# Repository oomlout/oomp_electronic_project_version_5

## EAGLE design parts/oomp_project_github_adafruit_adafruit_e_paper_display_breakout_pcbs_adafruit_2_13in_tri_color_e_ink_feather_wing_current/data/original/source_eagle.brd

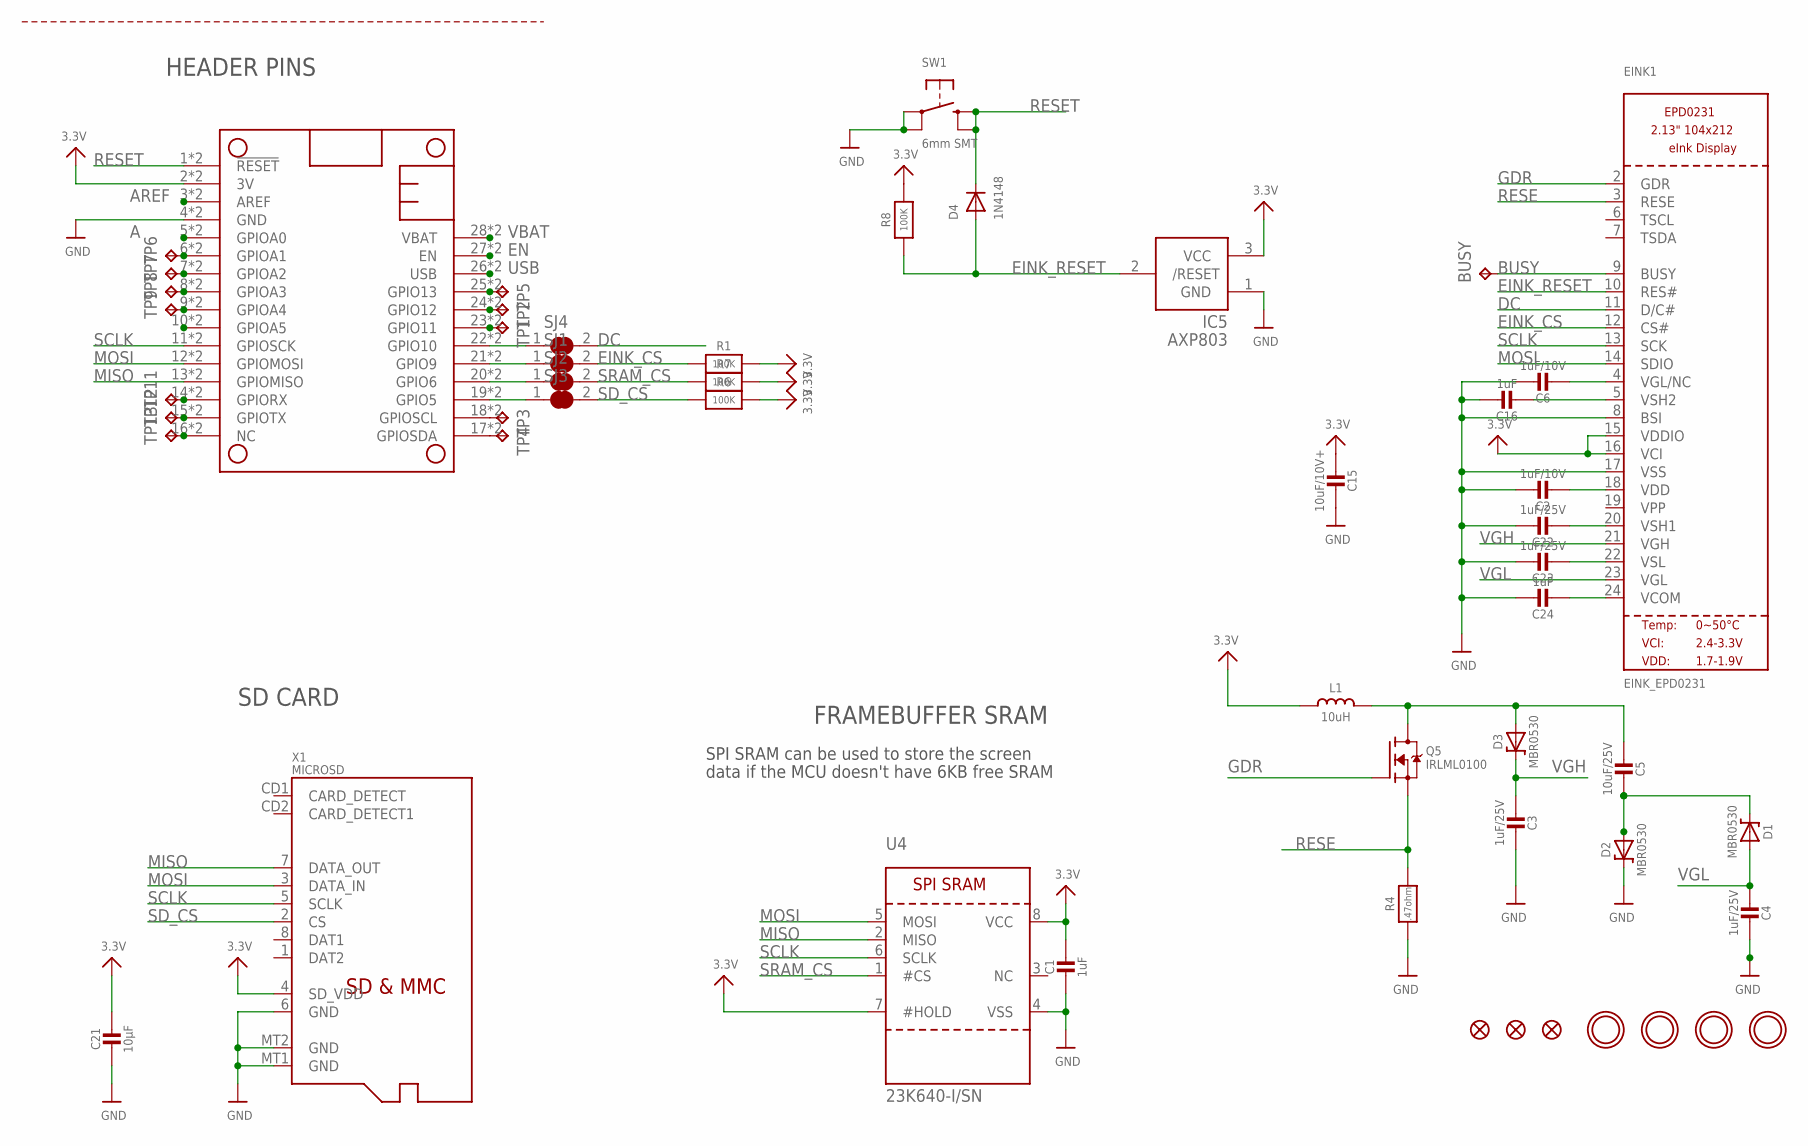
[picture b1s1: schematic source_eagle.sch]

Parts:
BUSY: TPTP15SQ; TP15SQ
C1: 1uF; 0805_10MGAP
C2, C6: 1uF/10V; 0805-NO
C3, C4, C22, C23: 1uF/25V; 0805-NO
C5: 10uF/25V; 0805-NO
C15: 10uF/10V+; 0805-NO
C16, C24: 1uF; 0805-NO
C21: 10µF; 0805-NO
D1, D2, D3: MBR0530; SOD-123
D4: 1N4148; SOD-323F
EINK1: EINK_EPD0231; EINK_213IN_104X212
FID1, FID2, FID3: FIDUCIAL_1MM
IC5: AXP803; SOT23
L1: 10uH; INDUCTOR_4X4MM_NR401
MS1: FEATHERWING_SMTDUALNOHOLES; FEATHERWING_SMT_NOHOLES
Q5: IRLML0100; SOT23-3
R1, R6, R7, R8: 100K; 0603-NO
R4: .47ohm; 0805_10MGAP
SJ1, SJ2, SJ3, SJ4: SOLDERJUMPER_CLOSED; SOLDERJUMPER_CLOSEDWIRE
SW1: 6mm SMT; EVQ-Q2_SMALLER
TP1, TP2, TP3, TP4, TP5, TP6, TP7, TP8, TP9, TP11, TP12, TP13: TPTP15SQ; TP15SQ
U4: 23K640-I/SN; SOIC8_150MIL
U$3, U$4, U$5, U$6: MOUNTINGHOLE2.5; MOUNTINGHOLE_2.5_PLATED
X1: MICROSD

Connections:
3.3V: C1.1, C15.2, C21.1, EINK1.15 (VDDIO), EINK1.16 (VCI), IC5.3 (VCC), L1.P$2 (2), MS1.2 (3V), MS1.2B (3V), R1.2, R6.2, R7.2, R8.2, U4.7 (#HOLD), U4.8 (VCC), X1.4 (SD_VDD)
A: MS1.5 (GPIOA0), MS1.5B (GPIOA0)
AREF: MS1.3 (AREF), MS1.3B (AREF)
B: MS1.6 (GPIOA1), MS1.6B (GPIOA1), TP6.TP
BUSY: BUSY.TP, EINK1.9 (BUSY)
C: MS1.7 (GPIOA2), MS1.7B (GPIOA2), TP7.TP
D: MS1.8 (GPIOA3), MS1.8B (GPIOA3), TP8.TP
DC: EINK1.11 (D/C#), SJ4.2
E: MS1.9 (GPIOA4), MS1.9B (GPIOA4), TP9.TP
EINK_CS: EINK1.12 (CS#), R1.1, SJ1.2
EINK_RESET: D4.A, EINK1.10 (RES#), IC5.2 (/RESET), R8.1
EN: MS1.27 (EN), MS1.27B (EN)
F: MS1.10 (GPIOA5), MS1.10B (GPIOA5)
G: MS1.16 (NC), MS1.16B (NC), TP13.TP
GDR: EINK1.2 (GDR), Q5.1 (G)
GND: C1.2, C2.1, C3.2, C4.2, C6.1, C15.1, C16.1, C21.2, C22.1, C23.1, C24.1, D2.C, EINK1.8 (BSI), EINK1.17 (VSS), IC5.1 (GND), MS1.4 (GND), MS1.4B (GND), R4.2, SW1.A, SW1.A' (P1), U4.4 (VSS), X1.6 (GND), X1.MT1 (GND), X1.MT2 (GND)
H: MS1.19 (GPIO5), MS1.19B (GPIO5), SJ3.1
I: MS1.20 (GPIO6), MS1.20B (GPIO6), SJ2.1
J: MS1.21 (GPIO9), MS1.21B (GPIO9), SJ1.1
K: MS1.22 (GPIO10), MS1.22B (GPIO10), SJ4.1
L: MS1.23 (GPIO11), MS1.23B (GPIO11), TP1.TP
M: MS1.24 (GPIO12), MS1.24B (GPIO12), TP2.TP
MISO: MS1.13 (GPIOMISO), MS1.13B (GPIOMISO), U4.2 (MISO), X1.7 (DATA_OUT)
MOSI: EINK1.14 (SDIO), MS1.12 (GPIOMOSI), MS1.12B (GPIOMOSI), U4.5 (MOSI), X1.3 (DATA_IN)
N: MS1.25 (GPIO13), MS1.25B (GPIO13), TP5.TP
unnamed: C5.2, D1.C, D2.A
unnamed: C5.1, D3.A, L1.P$1 (1), Q5.3 (D)
unnamed: C16.2, EINK1.5 (VSH2)
unnamed: C2.2, EINK1.18 (VDD)
unnamed: C22.2, EINK1.20 (VSH1)
unnamed: C6.2, EINK1.4 (VGL/NC)
unnamed: C23.2, EINK1.22 (VSL)
unnamed: C24.2, EINK1.24 (VCOM)
RESE: EINK1.3 (RESE), Q5.2 (S), R4.1
RESET: D4.C, MS1.1 (!RESET), MS1.1B (!RESET), SW1.B (S), SW1.B' (S1)
RX: MS1.14 (GPIORX), MS1.14B (GPIORX), TP11.TP
SCL: MS1.18 (GPIOSCL), MS1.18B (GPIOSCL), TP3.TP
SCLK: EINK1.13 (SCK), MS1.11 (GPIOSCK), MS1.11B (GPIOSCK), U4.6 (SCLK), X1.5 (SCLK)
SDA: MS1.17 (GPIOSDA), MS1.17B (GPIOSDA), TP4.TP
SD_CS: R6.1, SJ3.2, X1.2 (CS)
SRAM_CS: R7.1, SJ2.2, U4.1 (#CS)
TX: MS1.15 (GPIOTX), MS1.15B (GPIOTX), TP12.TP
USB: MS1.26 (USB), MS1.26B (USB)
VBAT: MS1.28 (VBAT), MS1.28B (VBAT)
VGH: C3.1, D3.C, EINK1.21 (VGH)
VGL: C4.1, D1.A, EINK1.23 (VGL)

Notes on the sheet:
HEADER PINS
FRAMEBUFFER SRAM
SPI SRAM can be used to store the screen
data if the MCU doesn't have 6KB free SRAM
SD CARD

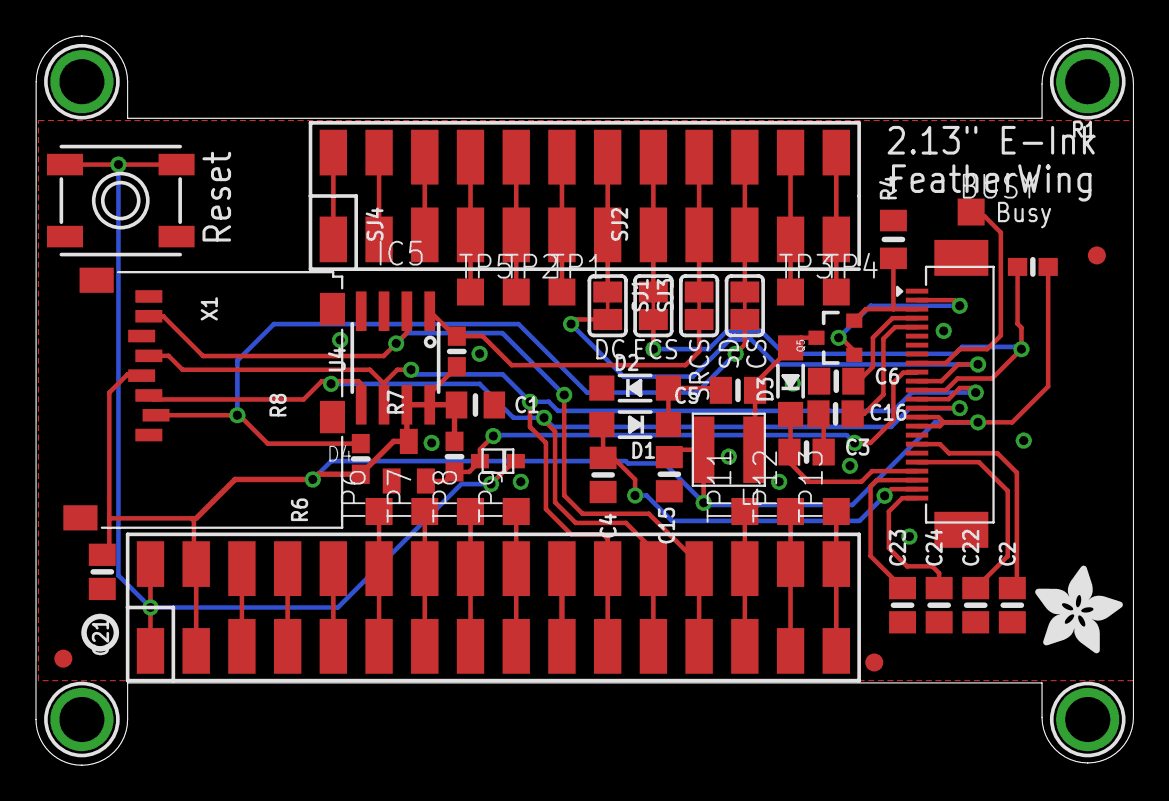
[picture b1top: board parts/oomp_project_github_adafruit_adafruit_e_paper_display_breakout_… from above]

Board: 2 copper layers, 61.0 x 40.5 mm, 55 parts (1 on the bottom side), 46 nets.

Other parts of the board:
U$8: ADAFRUIT_5MM
U$9: PCBFEAT-REV-040

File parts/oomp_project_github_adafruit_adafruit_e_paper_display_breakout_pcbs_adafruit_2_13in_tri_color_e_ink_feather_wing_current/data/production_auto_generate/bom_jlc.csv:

Comment,Designator,Footprint,LCSC Part #
,U$8,Adafruit 2.13in Tri-Color eInk FeatherWing-import-fps:ADAFRUIT_5MM,
,U$9,Adafruit 2.13in Tri-Color eInk FeatherWing-import-fps:PCBFEAT-REV-040,
.47ohm,R4,Adafruit 2.13in Tri-Color eInk FeatherWing-import-fps:0805_10MGAP,
100K,"R1,R6,R7,R8",Adafruit 2.13in Tri-Color eInk FeatherWing-import-fps:0603-NO,C25803
10uF/10V+,C15,Adafruit 2.13in Tri-Color eInk FeatherWing-import-fps:0805-NO,
10uF/25V,C5,Adafruit 2.13in Tri-Color eInk FeatherWing-import-fps:0805-NO,
10uH,L1,Adafruit 2.13in Tri-Color eInk FeatherWing-import-fps:INDUCTOR_4X4MM_NR401,
10µF,C21,Adafruit 2.13in Tri-Color eInk FeatherWing-import-fps:0805-NO,
1N4148,D4,Adafruit 2.13in Tri-Color eInk FeatherWing-import-fps:SOD-323F,
1uF,"C16,C24",Adafruit 2.13in Tri-Color eInk FeatherWing-import-fps:0805-NO,
1uF,C1,Adafruit 2.13in Tri-Color eInk FeatherWing-import-fps:0805_10MGAP,
1uF/10V,"C2,C6",Adafruit 2.13in Tri-Color eInk FeatherWing-import-fps:0805-NO,
1uF/25V,"C3,C4,C22,C23",Adafruit 2.13in Tri-Color eInk FeatherWing-import-fps:0805-NO,
23K640-I/SN,U4,Adafruit 2.13in Tri-Color eInk FeatherWing-import-fps:SOIC8_150MIL,
6mm SMT,SW1,Adafruit 2.13in Tri-Color eInk FeatherWing-import-fps:EVQ-Q2_SMALLER,
AXP803,IC5,Adafruit 2.13in Tri-Color eInk FeatherWing-import-fps:SOT23,
EINK_EPD0231,EINK1,Adafruit 2.13in Tri-Color eInk FeatherWing-import-fps:EINK_213IN_104X212,
FEATHERWING_SMTDUALNOHOLES,MS1,Adafruit 2.13in Tri-Color eInk FeatherWing-import-fps:FEATHERWING_SMT_NOHOLES,
IRLML0100,Q5,Adafruit 2.13in Tri-Color eInk FeatherWing-import-fps:SOT23-3,
MBR0530,"D1,D2,D3",Adafruit 2.13in Tri-Color eInk FeatherWing-import-fps:SOD-123,
MICROSD,X1,Adafruit 2.13in Tri-Color eInk FeatherWing-import-fps:MICROSD,
TPTP15SQ,"BUSY0,TP1,TP2,TP3,TP4,TP5,TP6,TP7,TP8,TP9,TP11,TP12,TP13",Adafruit 2.13in Tri-Color eInk FeatherWing-import-fps:TP15SQ,

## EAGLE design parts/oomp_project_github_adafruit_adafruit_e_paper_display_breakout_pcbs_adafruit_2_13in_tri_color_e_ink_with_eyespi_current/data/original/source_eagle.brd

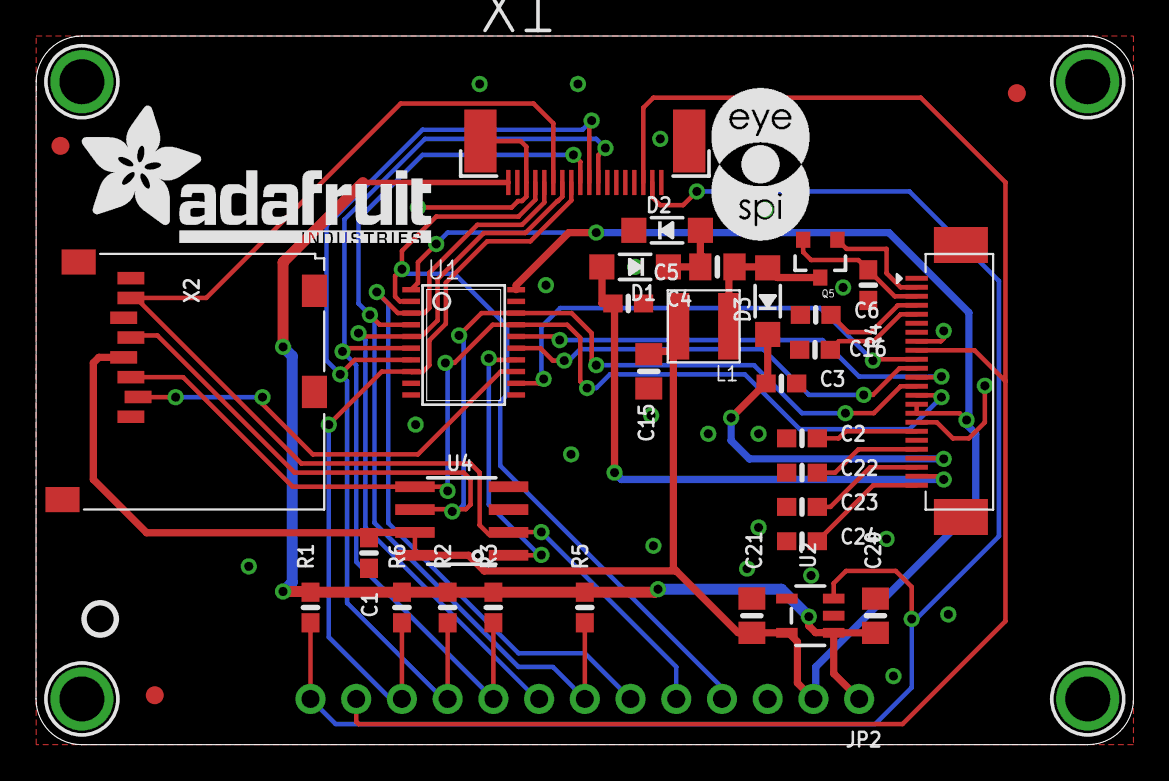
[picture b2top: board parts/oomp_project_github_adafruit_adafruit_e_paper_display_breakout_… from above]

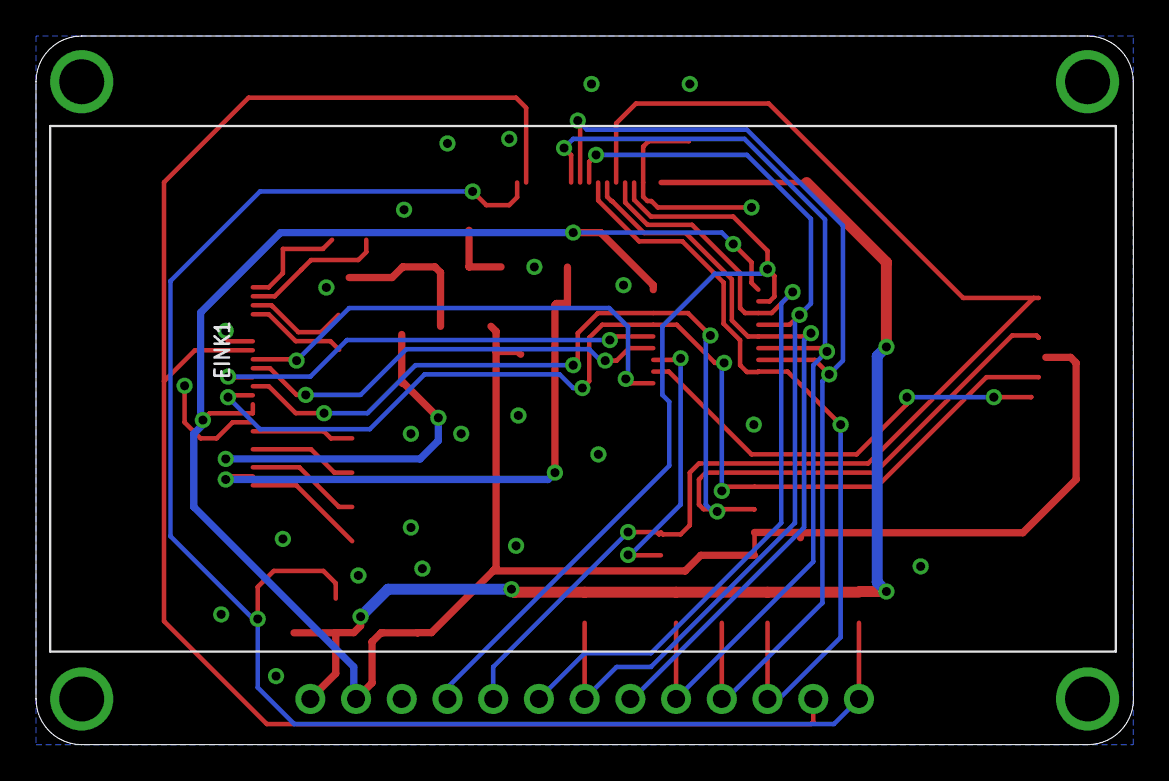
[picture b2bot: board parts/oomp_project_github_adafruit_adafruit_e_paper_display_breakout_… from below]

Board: 2 copper layers, 61.0 x 39.4 mm, 71 parts (16 on the bottom side), 32 nets.

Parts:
C1, C2, C3, C4, C6, C16, C22, C23, C24: 1uF/25V; 0603-NO
C5, C15, C20, C21: 10uF/16V; 0805-NO
D1, D2, D3: MBR0540; SOD-123
EINK1: EINK_24PIN_213IN; EINK_213IN_104X212
FID1, FID2, FID3: FIDUCIAL_1MM
JP2: 1X13_ROUND_70
L1: 10uH; INDUCTOR_4X4MM_NR401
PLABEL0: PLABEL0
PLABEL1: PLABEL1
PLABEL2: PLABEL2
PLABEL3: PLABEL3
PLABEL4: PLABEL4
PLABEL5: PLABEL5
PLABEL6: PLABEL6
PLABEL7: PLABEL7
PLABEL8: PLABEL8
PLABEL9: PLABEL9
PLABEL10: PLABEL10
PLABEL11: PLABEL11
PLABEL12: PLABEL12
PLABEL13: PLABEL13
PLABEL14: PLABEL14
PLABEL15: PLABEL15
PLABEL16: PLABEL16
PLABEL17: PLABEL17
PLABEL18: PLABEL18
PLABEL19: PLABEL19
PLABEL20: PLABEL20
PLABEL21: PLABEL21
PLABEL22: PLABEL22
PLABEL23: PLABEL23
PLABEL24: PLABEL24
PLABEL25: PLABEL25
PLABEL26: PLABEL26
PLABEL27: PLABEL27
PLABEL28: PLABEL28
PLABEL29: PLABEL29
Q5: IRLML0100; SOT23-3
R1, R2, R3, R5, R6: 100K; 0603-NO
R4: 0.47ohm; 0603-NO
U1: 74LVC245; TSSOP20
U2: AP2127K-3.3; SOT23-5
U4: 23K640-I/SN; SOIC8_150MIL
U$3, U$4, U$5, U$6: MOUNTINGHOLE2.5; MOUNTINGHOLE_2.5_PLATED
U$9: PCBFEAT-REV-040
U$28: ADAFRUIT_TEXT_20MM
U$35: EYESPI_MINI_LOGO
X1: EYE_SPI_DISPLAY_FLIP; EYE_SPI_DISPLAY_BOTCONTACT
X2: MICROSD

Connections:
3.3V: C1.1, C15.2, C21.1, EINK1.15, EINK1.16, JP2.2, L1.P$2, U1.1, U1.20, U2.5, U4.7, U4.8, X2.4
BUSY: EINK1.9, JP2.12, X1.16
DC: JP2.8, U1.5, X1.7
DC_3V: EINK1.11, U1.15
DISPCS: JP2.7, R5.1, U1.4, X1.9
DISPCS_3V: EINK1.12, U1.16
ENABLE: JP2.13, R1.1, U2.3, X1.17
GDR: EINK1.2, Q5.1
GND: C1.2, C2.1, C3.2, C4.2, C6.1, C15.1, C16.1, C20.2, C21.2, C22.1, C23.1, C24.1, D2.C, EINK1.8, EINK1.17, JP2.3, R4.2, U1.10, U1.19, U2.2, U4.4, X1.3, X1.SUPPORT1, X1.SUPPORT2, X2.6, X2.MT1, X2.MT2
MISO: JP2.5, U4.2, X1.6, X2.7
MOSI: JP2.6, U1.3, X1.5
MOSI_3V: EINK1.14, U1.17, U4.5, X2.3
unnamed: C5.2, D1.C, D2.A
unnamed: C5.1, D3.A, L1.P$1, Q5.3
unnamed: C16.2, EINK1.5
unnamed: C2.2, EINK1.18
unnamed: C22.2, EINK1.20
unnamed: C6.2, EINK1.4
unnamed: C23.2, EINK1.22
unnamed: C24.2, EINK1.24
RESE: EINK1.3, Q5.2, R4.1
RESET: JP2.11, R6.1, U1.8, X1.8
RESET_3V: EINK1.10, U1.12
SCLK: JP2.4, U1.2, X1.4
SCLK_3V: EINK1.13, U1.18, U4.6, X2.5
SDCS: JP2.10, R2.1, U1.7, X1.10
SDCS_3V: U1.13, X2.2
SRAMCS: JP2.9, R3.1, U1.6, X1.11
SRAMCS_3V: U1.14, U4.1
VGH: C3.1, D3.C, EINK1.21
VGL: C4.1, D1.A, EINK1.23
VIN: C20.1, JP2.1, R1.2, R2.2, R3.2, R5.2, R6.2, U2.1, X1.1

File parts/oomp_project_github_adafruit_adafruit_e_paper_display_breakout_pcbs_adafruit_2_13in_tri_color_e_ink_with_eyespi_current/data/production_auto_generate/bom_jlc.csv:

Comment,Designator,Footprint,LCSC Part #
,JP2,Adafruit 2.13in Tri-Color eInk with EYESPI-import-fps:1X13_ROUND_70,C2894936
,U$28,Adafruit 2.13in Tri-Color eInk with EYESPI-import-fps:ADAFRUIT_TEXT_20MM,
,U$35,Adafruit 2.13in Tri-Color eInk with EYESPI-import-fps:EYESPI_MINI_LOGO,
,U$9,Adafruit 2.13in Tri-Color eInk with EYESPI-import-fps:PCBFEAT-REV-040,
,PLABEL0,Adafruit 2.13in Tri-Color eInk with EYESPI-import-fps:PLABEL0,
,PLABEL1,Adafruit 2.13in Tri-Color eInk with EYESPI-import-fps:PLABEL1,
,PLABEL10,Adafruit 2.13in Tri-Color eInk with EYESPI-import-fps:PLABEL10,
,PLABEL11,Adafruit 2.13in Tri-Color eInk with EYESPI-import-fps:PLABEL11,
,PLABEL12,Adafruit 2.13in Tri-Color eInk with EYESPI-import-fps:PLABEL12,
,PLABEL13,Adafruit 2.13in Tri-Color eInk with EYESPI-import-fps:PLABEL13,
,PLABEL14,Adafruit 2.13in Tri-Color eInk with EYESPI-import-fps:PLABEL14,
,PLABEL15,Adafruit 2.13in Tri-Color eInk with EYESPI-import-fps:PLABEL15,
,PLABEL16,Adafruit 2.13in Tri-Color eInk with EYESPI-import-fps:PLABEL16,
,PLABEL17,Adafruit 2.13in Tri-Color eInk with EYESPI-import-fps:PLABEL17,
,PLABEL18,Adafruit 2.13in Tri-Color eInk with EYESPI-import-fps:PLABEL18,
,PLABEL19,Adafruit 2.13in Tri-Color eInk with EYESPI-import-fps:PLABEL19,
,PLABEL2,Adafruit 2.13in Tri-Color eInk with EYESPI-import-fps:PLABEL2,
,PLABEL20,Adafruit 2.13in Tri-Color eInk with EYESPI-import-fps:PLABEL20,
,PLABEL21,Adafruit 2.13in Tri-Color eInk with EYESPI-import-fps:PLABEL21,
,PLABEL22,Adafruit 2.13in Tri-Color eInk with EYESPI-import-fps:PLABEL22,
,PLABEL23,Adafruit 2.13in Tri-Color eInk with EYESPI-import-fps:PLABEL23,
,PLABEL24,Adafruit 2.13in Tri-Color eInk with EYESPI-import-fps:PLABEL24,
,PLABEL25,Adafruit 2.13in Tri-Color eInk with EYESPI-import-fps:PLABEL25,
,PLABEL26,Adafruit 2.13in Tri-Color eInk with EYESPI-import-fps:PLABEL26,
,PLABEL27,Adafruit 2.13in Tri-Color eInk with EYESPI-import-fps:PLABEL27,
,PLABEL28,Adafruit 2.13in Tri-Color eInk with EYESPI-import-fps:PLABEL28,
,PLABEL29,Adafruit 2.13in Tri-Color eInk with EYESPI-import-fps:PLABEL29,
,PLABEL3,Adafruit 2.13in Tri-Color eInk with EYESPI-import-fps:PLABEL3,
,PLABEL4,Adafruit 2.13in Tri-Color eInk with EYESPI-import-fps:PLABEL4,
,PLABEL5,Adafruit 2.13in Tri-Color eInk with EYESPI-import-fps:PLABEL5,
,PLABEL6,Adafruit 2.13in Tri-Color eInk with EYESPI-import-fps:PLABEL6,
,PLABEL7,Adafruit 2.13in Tri-Color eInk with EYESPI-import-fps:PLABEL7,
,PLABEL8,Adafruit 2.13in Tri-Color eInk with EYESPI-import-fps:PLABEL8,
,PLABEL9,Adafruit 2.13in Tri-Color eInk with EYESPI-import-fps:PLABEL9,
0.47ohm,R4,Adafruit 2.13in Tri-Color eInk with EYESPI-import-fps:0603-NO,
100K,"R1,R2,R3,R5,R6",Adafruit 2.13in Tri-Color eInk with EYESPI-import-fps:0603-NO,C25803
10uF/16V,"C5,C15,C20,C21",Adafruit 2.13in Tri-Color eInk with EYESPI-import-fps:0805-NO,
10uH,L1,Adafruit 2.13in Tri-Color eInk with EYESPI-import-fps:INDUCTOR_4X4MM_NR401,
1uF/25V,"C1,C2,C3,C4,C6,C16,C22,C23,C24",Adafruit 2.13in Tri-Color eInk with EYESPI-import-fps:0603-NO,C5673
23K640-I/SN,U4,Adafruit 2.13in Tri-Color eInk with EYESPI-import-fps:SOIC8_150MIL,
74LVC245,U1,Adafruit 2.13in Tri-Color eInk with EYESPI-import-fps:TSSOP20,
AP2127K-3.3,U2,Adafruit 2.13in Tri-Color eInk with EYESPI-import-fps:SOT23-5,
EINK_24PIN_213IN,EINK1,Adafruit 2.13in Tri-Color eInk with EYESPI-import-fps:EINK_213IN_104X212,
EYE_SPI_DISPLAY_FLIP,X1,Adafruit 2.13in Tri-Color eInk with EYESPI-import-fps:EYE_SPI_DISPLAY_BOTCONTACT,
IRLML0100,Q5,Adafruit 2.13in Tri-Color eInk with EYESPI-import-fps:SOT23-3,
MBR0540,"D1,D2,D3",Adafruit 2.13in Tri-Color eInk with EYESPI-import-fps:SOD-123,
MICROSD,X2,Adafruit 2.13in Tri-Color eInk with EYESPI-import-fps:MICROSD,

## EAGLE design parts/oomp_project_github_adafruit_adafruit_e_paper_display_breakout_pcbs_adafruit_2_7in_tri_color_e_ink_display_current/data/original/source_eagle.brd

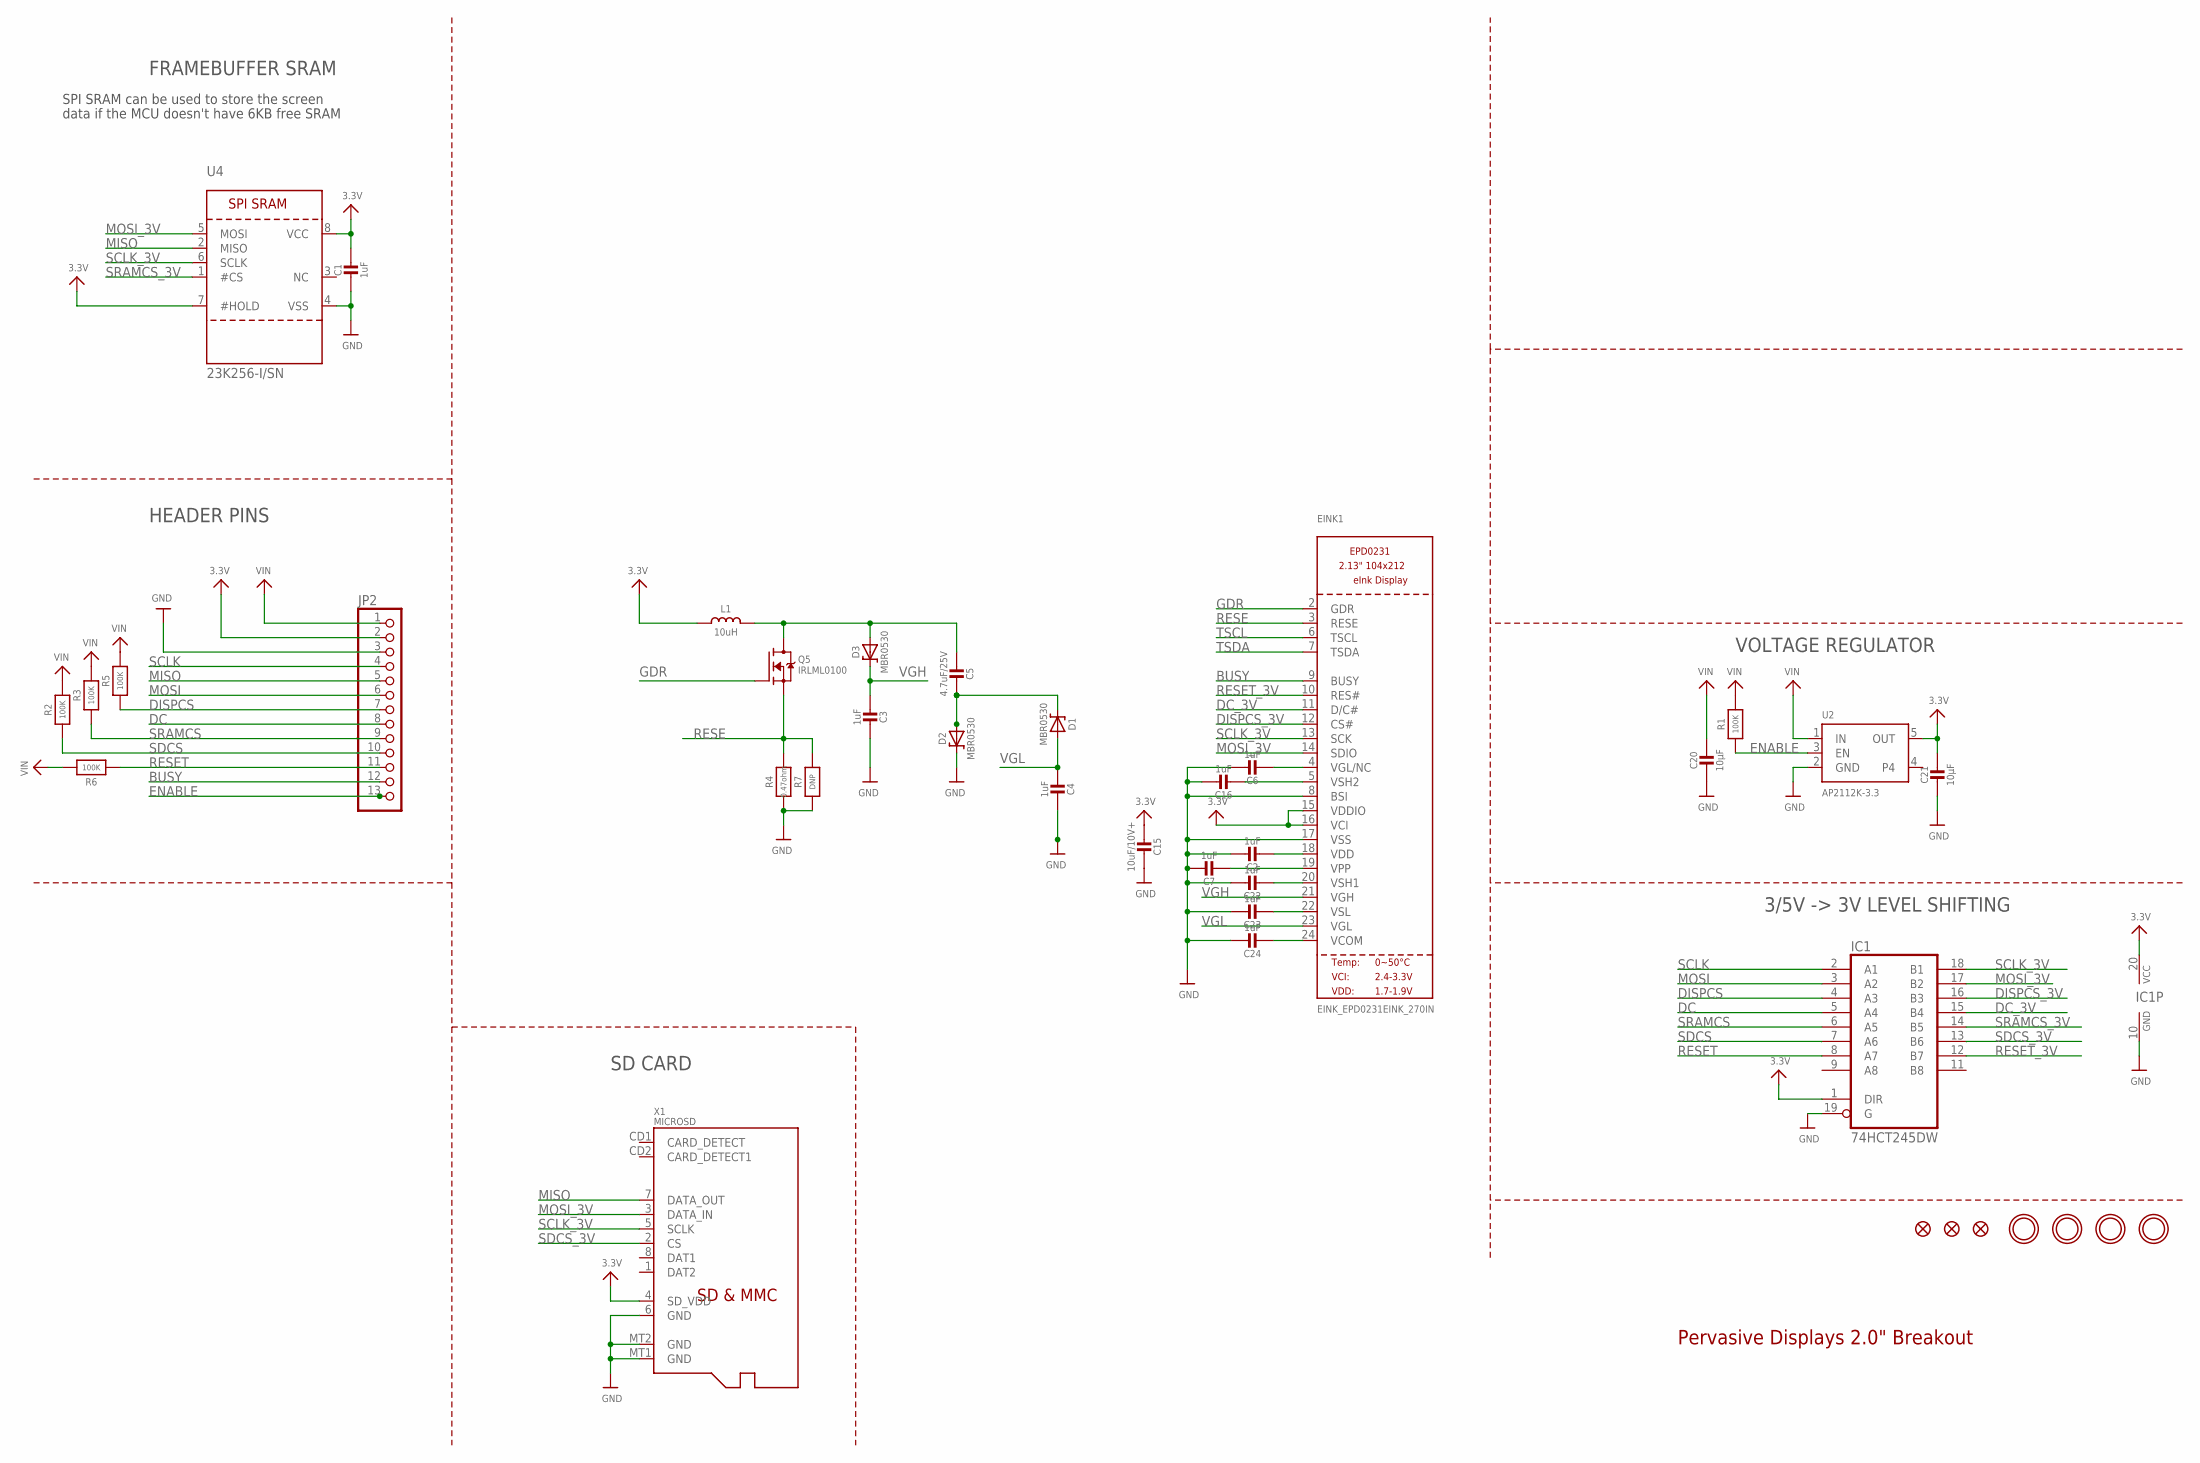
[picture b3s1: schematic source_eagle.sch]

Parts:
C1: 1uF; 0805_10MGAP
C2, C3, C4, C6, C7, C16, C22, C23, C24: 1uF; 0805-NO
C5: 4.7uF/25V; 0805-NO
C15: 10uF/10V+; 0805-NO
C20, C21: 10µF; 0805-NO
D1, D2, D3: MBR0530; SOD-123
EINK1: EINK_EPD0231EINK_270IN; EINK_270IN
FID1, FID2, FID3: FIDUCIAL_1MM
IC1: 74HCT245DW; SO20W
JP2: HEADER-1X13; 1X13_ROUND_70
L1: 10uH; INDUCTOR_4X4MM_NR401
Q5: IRLML0100; SOT23-3
R1, R2, R3, R5, R6: 100K; 0805-NO
R4: 0.47ohm; 0805_10MGAP
R7: DNP; 0805_10MGAP
U2: AP2112K-3.3; SOT23-5
U4: 23K256-I/SN; SOIC8_150MIL
U$3, U$4, U$5, U$6: MOUNTINGHOLE2.5; MOUNTINGHOLE_2.5_PLATED
X1: MICROSD

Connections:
3.3V: C1.1, C15.2, C21.1, EINK1.15 (VDDIO), EINK1.16 (VCI), IC1.1 (DIR), IC1.20 (VCC), JP2.2, L1.P$2 (2), U2.5 (OUT), U4.7 (#HOLD), U4.8 (VCC), X1.4 (SD_VDD)
BUSY: EINK1.9 (BUSY), JP2.12
DC: IC1.5 (A4), JP2.8
DC_3V: EINK1.11 (D/C#), IC1.15 (B4)
DISPCS: IC1.4 (A3), JP2.7, R5.1
DISPCS_3V: EINK1.12 (CS#), IC1.16 (B3)
ENABLE: JP2.13, R1.1, U2.3 (EN)
GDR: EINK1.2 (GDR), Q5.1 (G)
GND: C1.2, C2.1, C3.2, C4.2, C6.1, C7.1, C15.1, C16.1, C20.2, C21.2, C22.1, C23.1, C24.1, D2.C, EINK1.8 (BSI), EINK1.17 (VSS), IC1.10 (GND), IC1.19 (G), JP2.3, R4.2, R7.2, U2.2 (GND), U4.4 (VSS), X1.6 (GND), X1.MT1 (GND), X1.MT2 (GND)
MISO: JP2.5, U4.2 (MISO), X1.7 (DATA_OUT)
MOSI: IC1.3 (A2), JP2.6
MOSI_3V: EINK1.14 (SDIO), IC1.17 (B2), U4.5 (MOSI), X1.3 (DATA_IN)
unnamed: C7.2, EINK1.19 (VPP)
unnamed: C5.2, D1.C, D2.A
unnamed: C5.1, D3.A, L1.P$1 (1), Q5.3 (D)
unnamed: C16.2, EINK1.5 (VSH2)
unnamed: C2.2, EINK1.18 (VDD)
unnamed: C22.2, EINK1.20 (VSH1)
unnamed: C6.2, EINK1.4 (VGL/NC)
unnamed: C23.2, EINK1.22 (VSL)
unnamed: C24.2, EINK1.24 (VCOM)
RESE: EINK1.3 (RESE), Q5.2 (S), R4.1, R7.1
RESET: IC1.8 (A7), JP2.11, R6.1
RESET_3V: EINK1.10 (RES#), IC1.12 (B7)
SCLK: IC1.2 (A1), JP2.4
SCLK_3V: EINK1.13 (SCK), IC1.18 (B1), U4.6 (SCLK), X1.5 (SCLK)
SDCS: IC1.7 (A6), JP2.10, R2.1
SDCS_3V: IC1.13 (B6), X1.2 (CS)
SRAMCS: IC1.6 (A5), JP2.9, R3.1
SRAMCS_3V: IC1.14 (B5), U4.1 (#CS)
TSCL: EINK1.6 (TSCL)
TSDA: EINK1.7 (TSDA)
VGH: C3.1, D3.C, EINK1.21 (VGH)
VGL: C4.1, D1.A, EINK1.23 (VGL)
VIN: C20.1, JP2.1, R1.2, R2.2, R3.2, R5.2, R6.2, U2.1 (IN)

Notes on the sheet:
Pervasive Displays 2.0" Breakout
VOLTAGE REGULATOR
3/5V -> 3V LEVEL SHIFTING
HEADER PINS
FRAMEBUFFER SRAM
SPI SRAM can be used to store the screen
data if the MCU doesn't have 6KB free SRAM
SD CARD

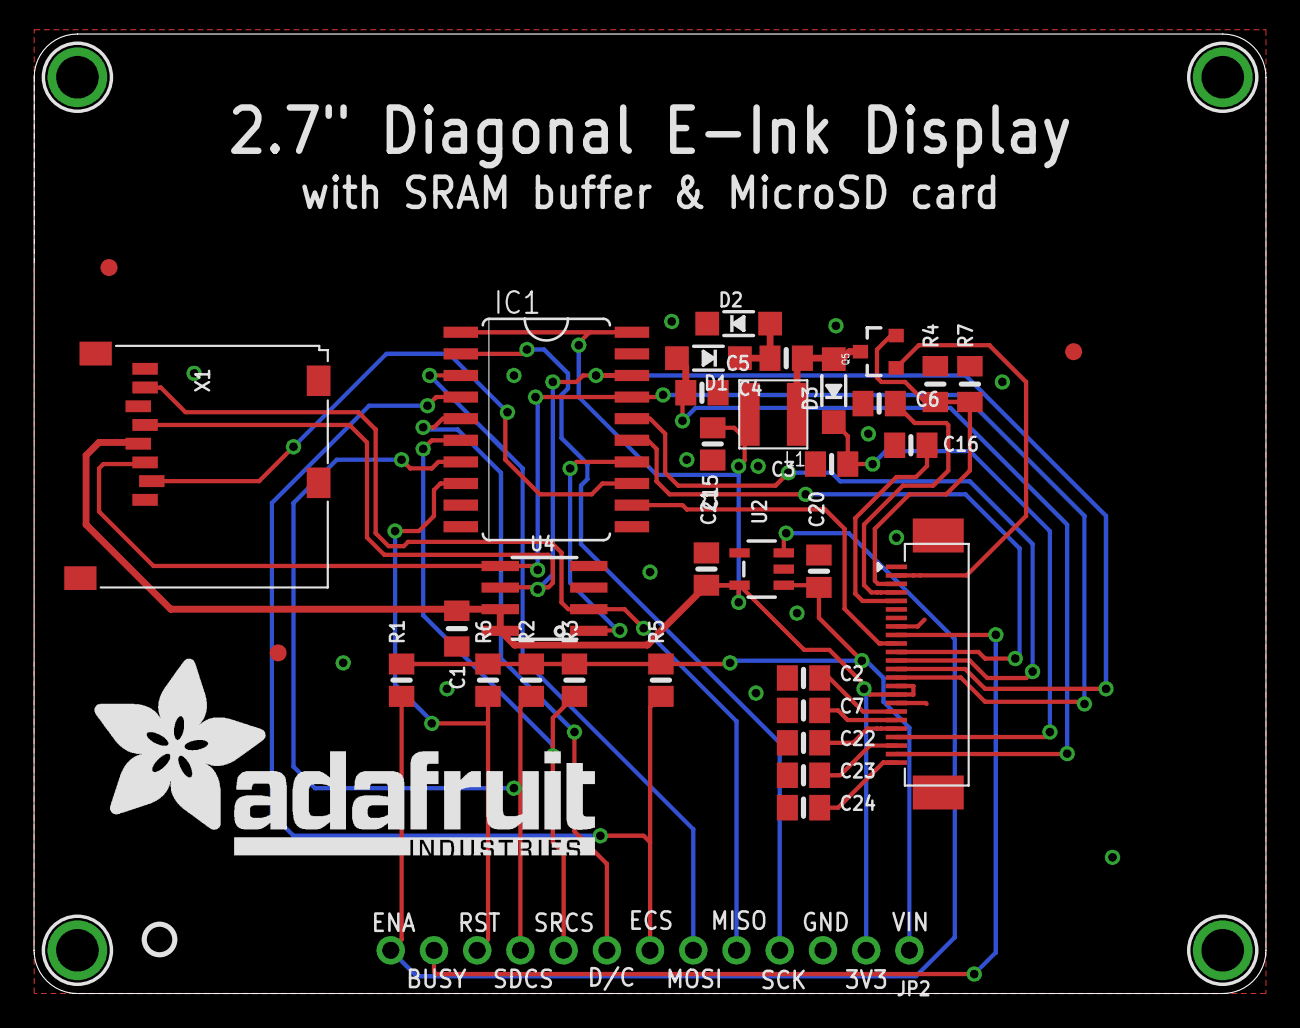
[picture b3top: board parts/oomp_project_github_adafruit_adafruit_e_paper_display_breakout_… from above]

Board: 2 copper layers, 72.4 x 56.4 mm, 41 parts (1 on the bottom side), 33 nets.

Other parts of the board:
U$9: PCBFEAT-REV-040
U$39: ADAFRUIT_TEXT_30MM

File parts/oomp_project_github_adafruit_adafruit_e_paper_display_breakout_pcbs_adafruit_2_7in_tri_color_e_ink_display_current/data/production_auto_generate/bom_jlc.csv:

Comment,Designator,Footprint,LCSC Part #
,JP2,Adafruit 2.7in Tri-Color eInk Display-import-fps:1X13_ROUND_70,C2894936
,U$39,Adafruit 2.7in Tri-Color eInk Display-import-fps:ADAFRUIT_TEXT_30MM,
,U$9,Adafruit 2.7in Tri-Color eInk Display-import-fps:PCBFEAT-REV-040,
0.47ohm,R4,Adafruit 2.7in Tri-Color eInk Display-import-fps:0805_10MGAP,
100K,"R1,R2,R3,R5,R6",Adafruit 2.7in Tri-Color eInk Display-import-fps:0805-NO,C149504
10uF/10V+,C15,Adafruit 2.7in Tri-Color eInk Display-import-fps:0805-NO,
10uH,L1,Adafruit 2.7in Tri-Color eInk Display-import-fps:INDUCTOR_4X4MM_NR401,
10µF,"C20,C21",Adafruit 2.7in Tri-Color eInk Display-import-fps:0805-NO,
1uF,"C2,C3,C4,C6,C7,C16,C22,C23,C24",Adafruit 2.7in Tri-Color eInk Display-import-fps:0805-NO,
1uF,C1,Adafruit 2.7in Tri-Color eInk Display-import-fps:0805_10MGAP,
23K256-I/SN,U4,Adafruit 2.7in Tri-Color eInk Display-import-fps:SOIC8_150MIL,
4.7uF/25V,C5,Adafruit 2.7in Tri-Color eInk Display-import-fps:0805-NO,
74HCT245DW,IC1,Adafruit 2.7in Tri-Color eInk Display-import-fps:SO20W,
AP2112K-3.3,U2,Adafruit 2.7in Tri-Color eInk Display-import-fps:SOT23-5,
DNP,R7,Adafruit 2.7in Tri-Color eInk Display-import-fps:0805_10MGAP,
EINK_EPD0231EINK_270IN,EINK1,Adafruit 2.7in Tri-Color eInk Display-import-fps:EINK_270IN,
IRLML0100,Q5,Adafruit 2.7in Tri-Color eInk Display-import-fps:SOT23-3,
MBR0530,"D1,D2,D3",Adafruit 2.7in Tri-Color eInk Display-import-fps:SOD-123,
MICROSD,X1,Adafruit 2.7in Tri-Color eInk Display-import-fps:MICROSD,

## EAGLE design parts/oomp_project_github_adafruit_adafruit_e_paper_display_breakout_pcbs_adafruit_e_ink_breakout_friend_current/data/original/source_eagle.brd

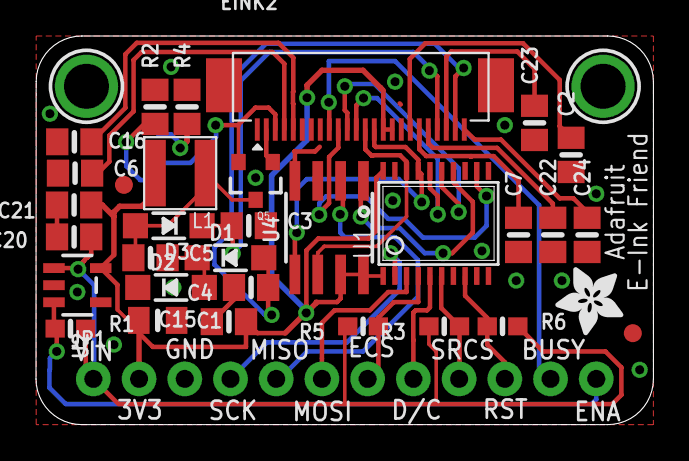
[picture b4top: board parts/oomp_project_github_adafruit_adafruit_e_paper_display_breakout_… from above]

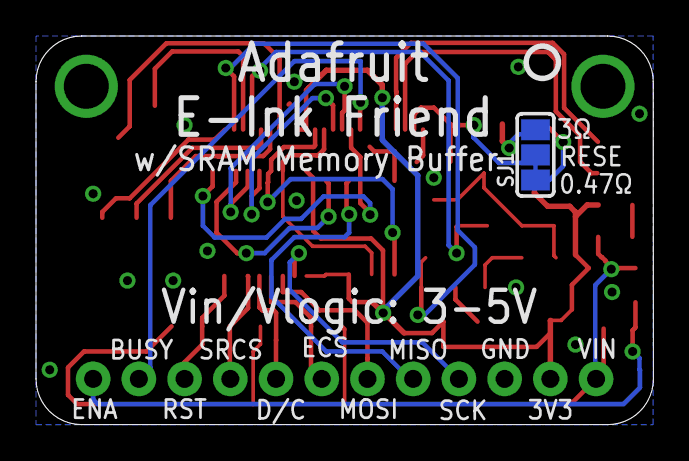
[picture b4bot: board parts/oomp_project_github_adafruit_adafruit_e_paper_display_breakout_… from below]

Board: 2 copper layers, 34.3 x 21.6 mm, 37 parts (2 on the bottom side), 32 nets.

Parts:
C1: 1uF; 0805_10MGAP
C2, C3, C4, C6, C7, C16, C22, C23, C24: 1uF; 0805-NO
C5, C15: 10uF; 0805-NO
C20, C21: 10µF; 0805-NO
D1, D2, D3: MBR0530; SOD-123
EINK2: EINK_24PIN_CONNECTOR; EINK_24PIN
FID2, FID3: FIDUCIAL_1MM
JP1: 1X12_ROUND_76MIL
L1: 10uH; INDUCTOR_4X4MM_NR401
Q5: IRLML0100; SOT23-3
R1, R3, R5, R6: 100K; 0603-NO
R2: 0.47ohm; 0805-NO
R4: 3 ohm; 0805-NO
SJ1: SOLDERJUMPER_2WAY_OPEN_NOPASTE
U1: TSSOP20
U2: AP2112K-3.3; SOT23-5
U4: 23K256-I/SN; SOIC8_150MIL
U$2: ADAFRUIT_3.5MM
U$3, U$4: MOUNTINGHOLE2.5; MOUNTINGHOLE_2.5_PLATED
U$9: PCBFEAT-REV-040

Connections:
3.3V: C1.1, C15.2, C21.1, EINK2.15, EINK2.16, JP1.2, L1.P$2, U1.1, U1.20, U2.5, U4.7, U4.8
BUSY: EINK2.9, JP1.11
DC: JP1.8, U1.5
DC_3V: EINK2.11, U1.15
DISPCS: JP1.7, R5.1, U1.4
DISPCS_3V: EINK2.12, U1.16
ENABLE: JP1.12, R1.1, U2.3
GDR: EINK2.2, Q5.1
GND: C1.2, C2.1, C3.2, C4.2, C6.1, C7.1, C15.1, C16.1, C20.2, C21.2, C22.1, C23.1, C24.1, D2.C, EINK2.8, EINK2.17, JP1.3, R2.2, R4.2, U1.10, U1.19, U2.2, U4.4
MISO: JP1.5, U4.2
MOSI: JP1.6, U1.3
MOSI_3V: EINK2.14, U1.17, U4.5
unnamed: C7.2, EINK2.19
unnamed: C5.2, D1.C, D2.A
unnamed: C5.1, D3.A, L1.P$1, Q5.3
unnamed: C16.2, EINK2.5
unnamed: C2.2, EINK2.18
unnamed: C22.2, EINK2.20
unnamed: R4.1, SJ1.3
unnamed: C6.2, EINK2.4
unnamed: C23.2, EINK2.22
unnamed: C24.2, EINK2.24
RESE: EINK2.3, Q5.2, R2.1, SJ1.1, SJ1.2
RESET: JP1.10, R6.1, U1.8
RESET_3V: EINK2.10, U1.12
SCLK: JP1.4, U1.2
SCLK_3V: EINK2.13, U1.18, U4.6
SRAMCS: JP1.9, R3.1, U1.6
SRAMCS_3V: U1.14, U4.1
VGH: C3.1, D3.C, EINK2.21
VGL: C4.1, D1.A, EINK2.23
VIN: C20.1, JP1.1, R1.2, R3.2, R5.2, R6.2, U2.1

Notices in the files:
parts and their libraries:
microbuilder: This work is placed in the public domain, and may be freely used for commercial and non-commercial work with the following conditions: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
